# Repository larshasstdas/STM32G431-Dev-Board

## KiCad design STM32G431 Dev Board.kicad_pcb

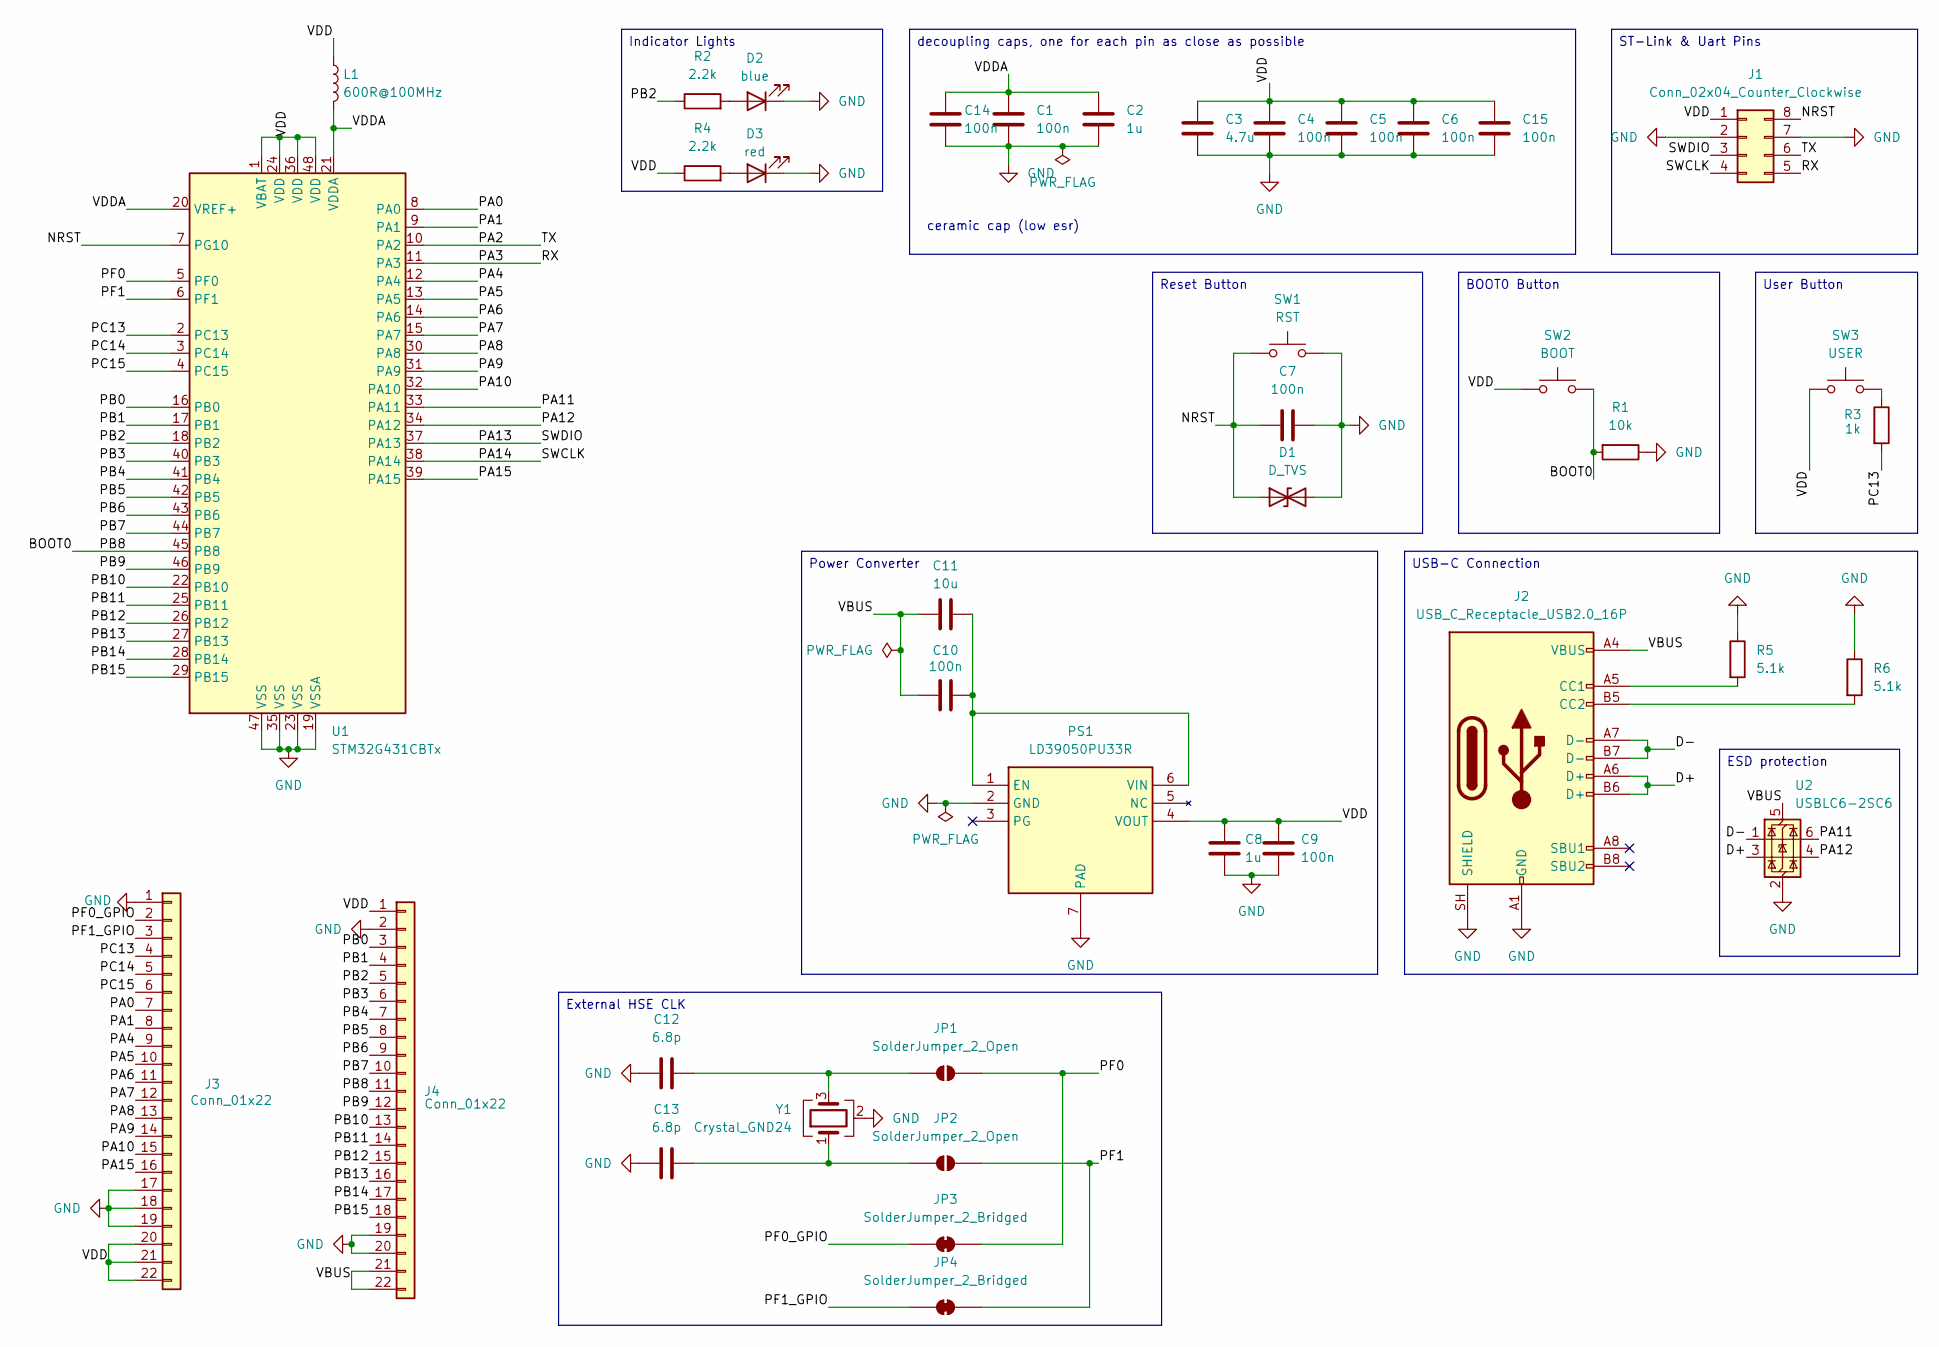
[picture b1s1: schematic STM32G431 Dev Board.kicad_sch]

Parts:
C1, C4, C5, C6, C7, C9, C10, C14, C15: 100n; C_0603_1608Metric
C2, C8: 1u; C_0603_1608Metric
C3: 4.7u; C_0805_2012Metric
C11: 10u; C_0805_2012Metric
C12, C13: 6.8p; C_0402_1005Metric
D1: D_TVS; D_SOD-323
D2: blue; LED_0603_1608Metric
D3: red; LED_0603_1608Metric
J1: Conn_02x04_Counter_Clockwise; PinHeader_2x04_P2.54mm_Horizontal
J2: USB_C_Receptacle_USB2.0_16P; USB_C_Receptacle_HRO_TYPE-C-31-M-12
J3, J4: Conn_01x22; PinHeader_1x22_P2.54mm_Vertical
JP1, JP2: SolderJumper_2_Open; SolderJumper-2_P1.3mm_Open_Pad1.0x1.5mm
JP3, JP4: SolderJumper_2_Bridged; SolderJumper-2_P1.3mm_Bridged2Bar_Pad1.0x1.5mm
L1: 600R@100MHz; L_0603_1608Metric
PS1: LD39050PU33R; SON95P300X300X100-7N-D; Manufacturer_Part_Number LD39050PU33R; Mouser Part Number 511-LD39050PU33R
R1: 10k; R_0603_1608Metric
R2, R4: 2.2k; R_0603_1608Metric
R3: 1k; R_0603_1608Metric
R5, R6: 5.1k; R_0603_1608Metric
SW1: RST; SW_SPST_TL3342
SW2: BOOT; SW_SPST_TL3342
SW3: USER; SW_SPST_TL3342
U1: STM32G431CBTx; LQFP-48_7x7mm_P0.5mm
U2: USBLC6-2SC6; SOT-23-6
Y1: Crystal_GND24; Crystal_SMD_3225-4Pin_3.2x2.5mm

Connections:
/BOOT0: J4.11, R1.2, SW2.2, U1.45 (PB8)
/D+: J2.A6 (D+), J2.B6 (D+), U2.3 (I/O2)
/D-: J2.A7 (D-), J2.B7 (D-), U2.1 (I/O1)
/NRST: C7.1, D1.1 (A1), J1.8, SW1.1, U1.7 (PG10)
/PA0: J3.7, U1.8 (PA0)
/PA1: J3.8, U1.9 (PA1)
/PA2: J1.6, U1.10 (PA2)
/PA3: J1.5, U1.11 (PA3)
/PA4: J3.9, U1.12 (PA4)
/PA5: J3.10, U1.13 (PA5)
/PA6: J3.11, U1.14 (PA6)
/PA7: J3.12, U1.15 (PA7)
/PA8: J3.13, U1.30 (PA8)
/PA9: J3.14, U1.31 (PA9)
/PA10: J3.15, U1.32 (PA10)
/PA11: U1.33 (PA11), U2.6 (I/O1)
/PA12: U1.34 (PA12), U2.4 (I/O2)
/PA13: J1.3, U1.37 (PA13)
/PA14: J1.4, U1.38 (PA14)
/PA15: J3.16, U1.39 (PA15)
/PB0: J4.3, U1.16 (PB0)
/PB1: J4.4, U1.17 (PB1)
/PB2: J4.5, R2.1, U1.18 (PB2)
/PB3: J4.6, U1.40 (PB3)
/PB4: J4.7, U1.41 (PB4)
/PB5: J4.8, U1.42 (PB5)
/PB6: J4.9, U1.43 (PB6)
/PB7: J4.10, U1.44 (PB7)
/PB9: J4.12, U1.46 (PB9)
/PB10: J4.13, U1.22 (PB10)
/PB11: J4.14, U1.25 (PB11)
/PB12: J4.15, U1.26 (PB12)
/PB13: J4.16, U1.27 (PB13)
/PB14: J4.17, U1.28 (PB14)
/PB15: J4.18, U1.29 (PB15)
/PC13: J3.4, R3.2, U1.2 (PC13)
/PC14: J3.5, U1.3 (PC14)
/PC15: J3.6, U1.4 (PC15)
/PF0: JP1.2 (B), JP3.2 (B), U1.5 (PF0)
/PF0_GPIO: J3.2, JP3.1 (A)
/PF1: JP2.2 (B), JP4.2 (B), U1.6 (PF1)
/PF1_GPIO: J3.3, JP4.1 (A)
/VBUS: C10.1, C11.1, J2.A4 (VBUS), J2.A9 (VBUS), J2.B4 (VBUS), J2.B9 (VBUS), J4.21, J4.22, U2.5 (VBUS)
/VDD: C3.1, C4.1, C5.1, C6.1, C8.1, C9.1, C15.1, J1.1, J3.20, J3.21, J3.22, J4.1, L1.1, PS1.4 (VOUT), R4.1, SW2.1, SW3.1, U1.1 (VBAT), U1.24 (VDD), U1.36 (VDD), U1.48 (VDD)
/VDDA: C1.1, C2.1, C14.1, L1.2, U1.20 (VREF+), U1.21 (VDDA)
GND: C1.2, C2.2, C3.2, C4.2, C5.2, C6.2, C7.2, C8.2, C9.2, C12.1, C13.1, C14.2, C15.2, D1.2 (A2), D2.1 (K), D3.1 (K), J1.2, J1.7, J2.A1 (GND), J2.A12 (GND), J2.B1 (GND), J2.B12 (GND), J2.SH (SHIELD), J3.1, J3.17, J3.18, J3.19, J4.2, J4.19, J4.20, PS1.2 (GND), PS1.7 (PAD), R1.1, R5.1, R6.1, SW1.2, U1.19 (VSSA), U1.23 (VSS), U1.35 (VSS), U1.47 (VSS), U2.2 (GND), Y1.2 (G), Y1.4 (G)
unnamed: D2.2 (A), R2.2
unnamed: D3.2 (A), R4.2
unnamed: J2.A5 (CC1), R5.2
unnamed: J2.B5 (CC2), R6.2
unnamed: C12.2, JP1.1 (A), Y1.3
unnamed: C13.2, JP2.1 (A), Y1.1
unnamed: C10.2, C11.2, PS1.1 (EN), PS1.6 (VIN)
unnamed: R3.1, SW3.2

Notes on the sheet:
ceramic cap (low esr)
External HSE CLK
Indicator Lights
User Button
Reset Button
decoupling caps, one for each pin as close as possible
ESD protection
BOOT0 Button
Power Converter
ST-Link & Uart Pins
USB-C Connection

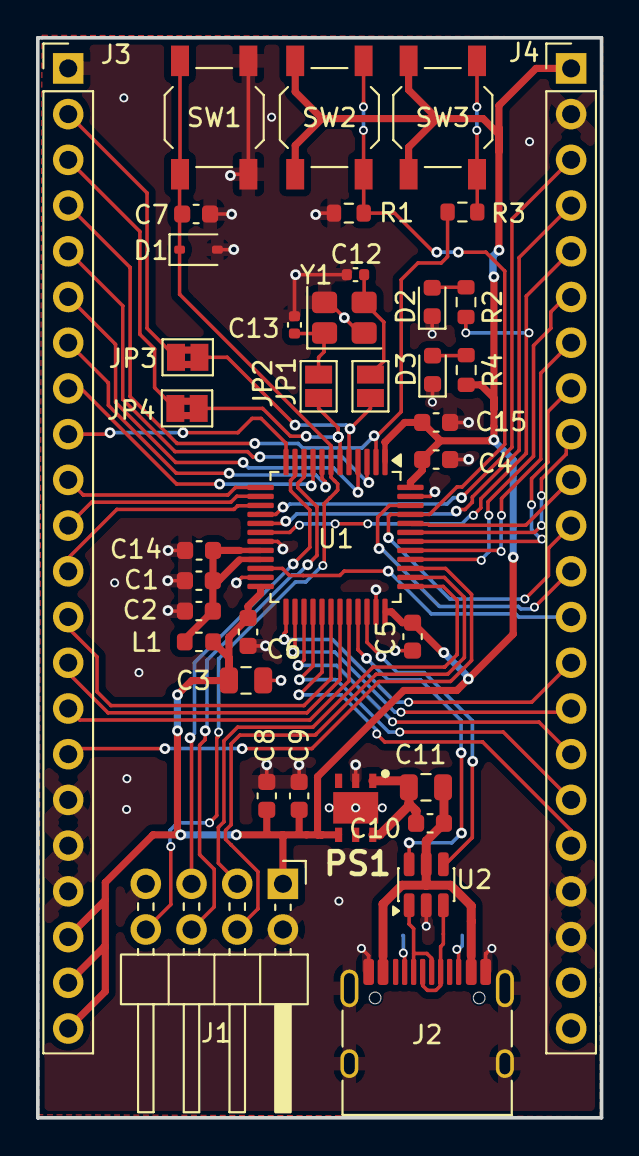
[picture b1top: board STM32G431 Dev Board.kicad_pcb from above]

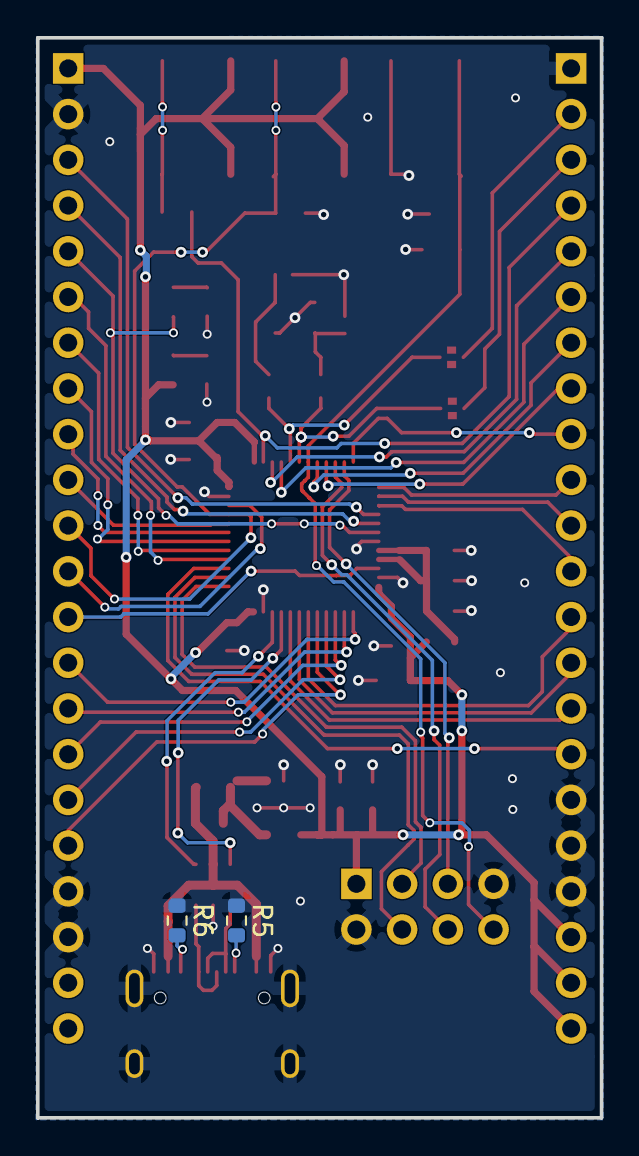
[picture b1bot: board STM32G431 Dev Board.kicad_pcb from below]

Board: 2 copper layers, 31.3 x 60.0 mm, 40 parts (2 on the bottom side), 54 nets.

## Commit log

2026-06-07 start projekt
2026-06-26 first layout
2026-06-27 changed pin order
2026-06-28 most routing done
